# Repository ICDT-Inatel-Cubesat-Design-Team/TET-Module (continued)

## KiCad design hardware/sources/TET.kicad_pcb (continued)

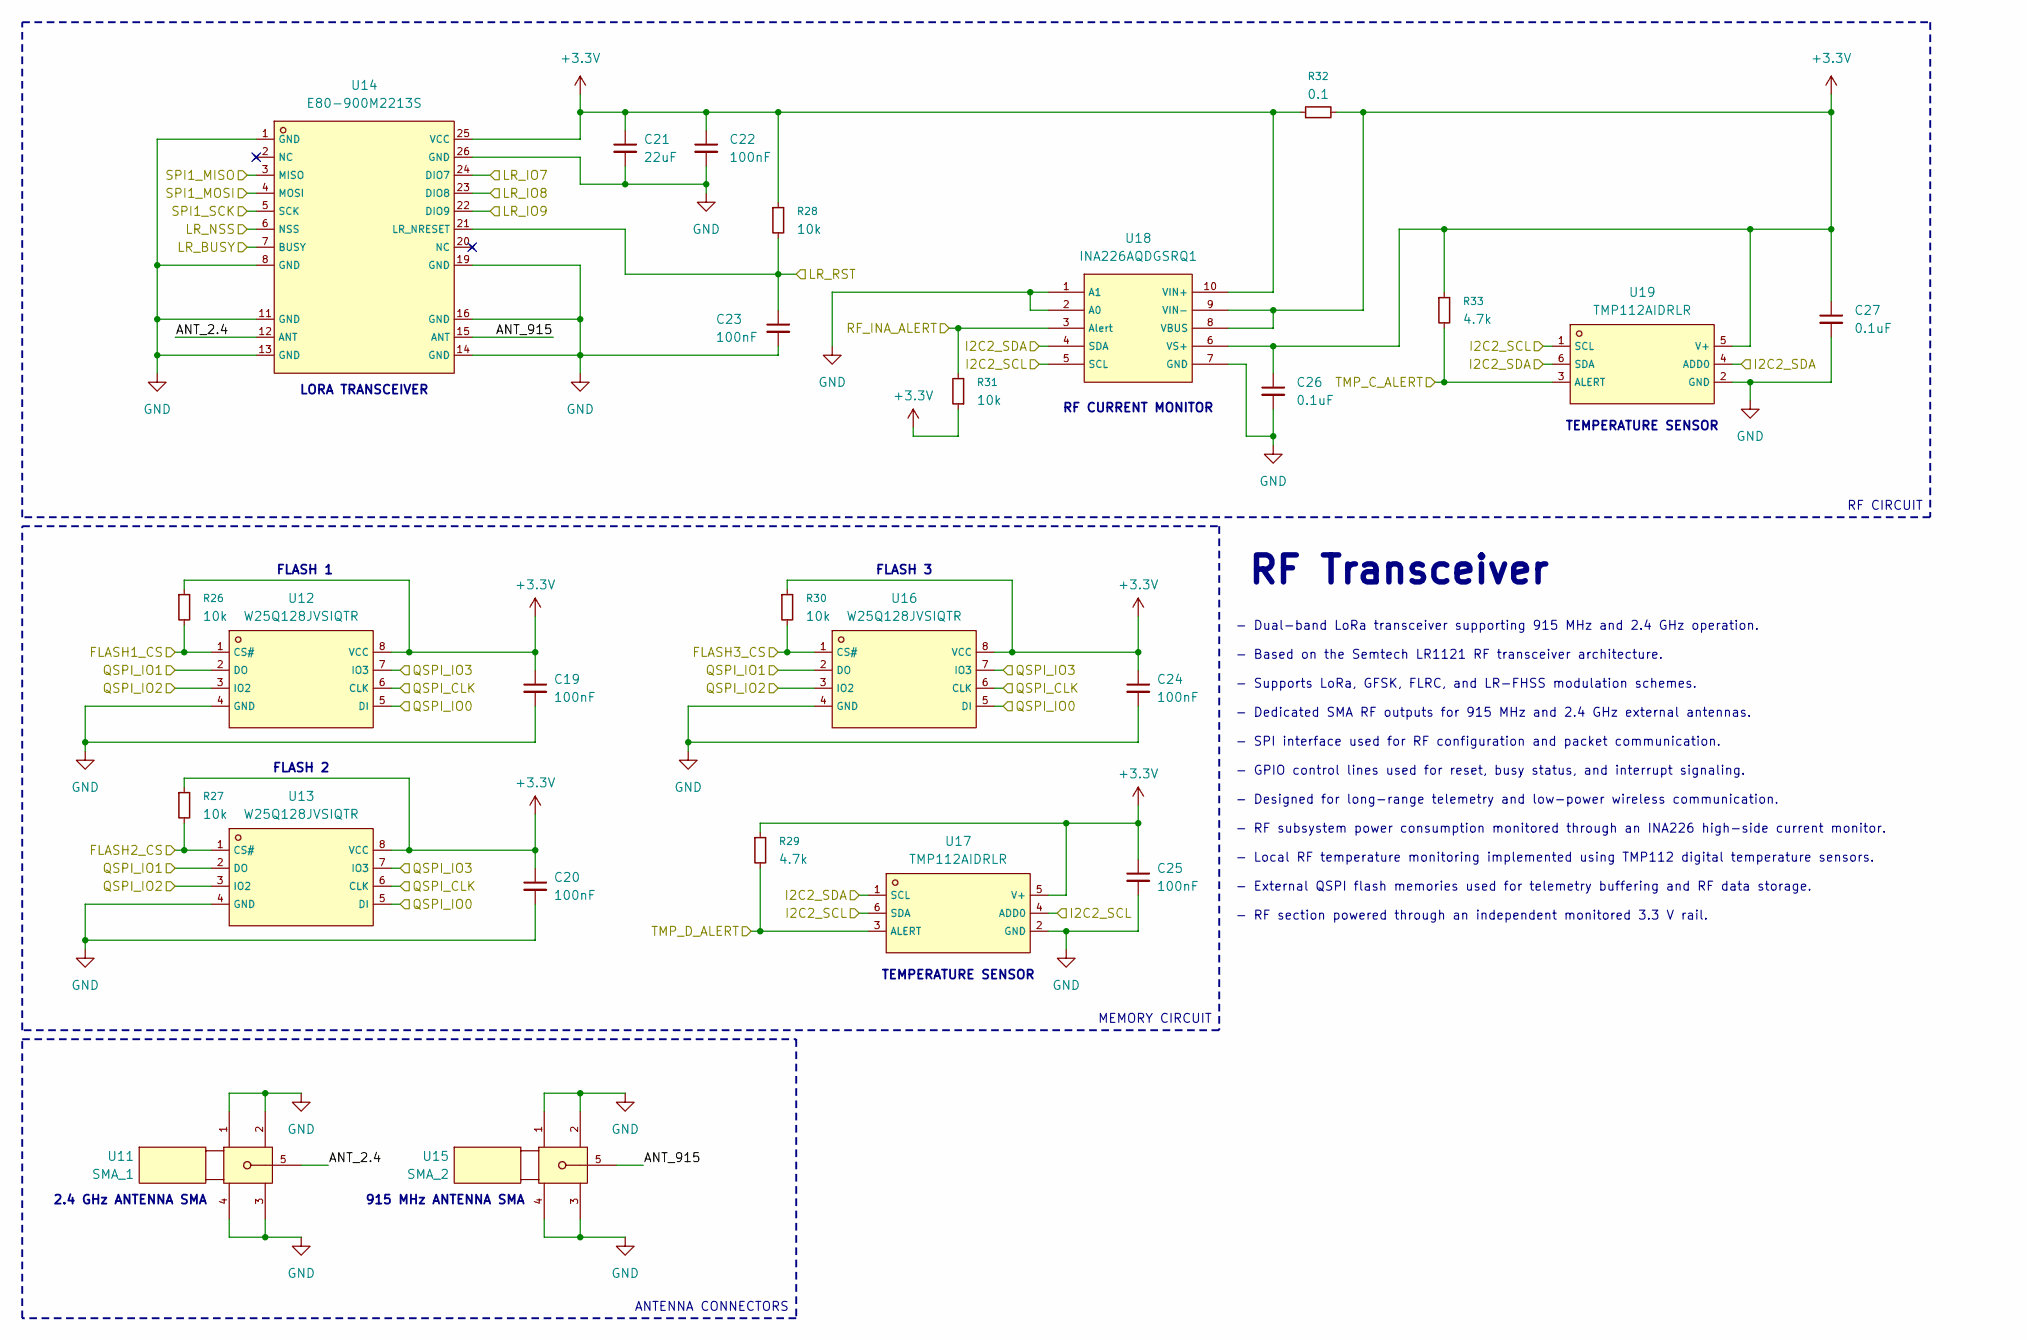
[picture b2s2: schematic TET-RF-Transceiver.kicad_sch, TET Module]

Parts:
C19, C20, C22, C23, C24, C25: 100nF; C_0603_1608Metric
C21: 22uF; C_0603_1608Metric
C26, C27: 0.1uF; C_0603_1608Metric
R26, R27, R28, R30, R31: 10k; R_0603_1608Metric
R29, R33: 4.7k; R_0603_1608Metric
R32: 0.1; R_1206_3216Metric
U11: SMA_1; SMA-TH_SMA-KWE_C7498154; LCSC C7498154
U12, U13, U16: W25Q128JVSIQTR; SOIC-8_L5.3-W5.3-P1.27-LS8.0-BL; LCSC C97521
U14: E80-900M2213S; WIFIM-SMD_22P-L26.0-W16.0-P1.27-TL; LCSC C42464134
U15: SMA_2; SMA-TH_SMA-KWE_C7498154; LCSC C7498154
U17, U19: TMP112AIDRLR; SOT-563_L1.6-W1.2-P0.50-LS1.6-BR; LCSC C28927
U18: INA226AQDGSRQ1; VSSOP-10_L3.0-W3.0-P0.50-LS4.9-BL; LCSC C2653835

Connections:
+3.3V: C19.1, C20.1, C21.1, C22.1, C24.1, C25.1, C26.1, C27.1, R26.1, R27.1, R28.1, R29.1, R30.1, R31.1, R32.1, R32.2, R33.1, U12.8 (VCC), U13.8 (VCC), U14.25 (VCC), U16.8 (VCC), U17.5 (V+), U18.6 (VS+), U18.8 (VBUS), U18.9 (VIN-), U18.10 (VIN+), U19.5 (V+); also elsewhere on the board
/FLASH1_CS: R26.2, U12.1 (CS#); also elsewhere on the board
/FLASH2_CS: R27.2, U13.1 (CS#); also elsewhere on the board
/FLASH3_CS: R30.2, U16.1 (CS#); also elsewhere on the board
/I2C2_SCL: U17.4 (ADD0), U17.6 (SDA), U18.5 (SCL), U19.1 (SCL); also elsewhere on the board
/I2C2_SDA: U17.1 (SCL), U18.4 (SDA), U19.4 (ADD0), U19.6 (SDA); also elsewhere on the board
/LR_BUSY: U14.7 (BUSY); also elsewhere on the board
/LR_IO7: U14.24 (DIO7); also elsewhere on the board
/LR_IO8: U14.23 (DIO8); also elsewhere on the board
/LR_IO9: U14.22 (DIO9); also elsewhere on the board
/LR_NSS: U14.6 (NSS); also elsewhere on the board
/LR_RST: C23.1, R28.2, U14.21 (LR_NRESET); also elsewhere on the board
/QSPI_CLK: U12.6 (CLK), U13.6 (CLK), U16.6 (CLK); also elsewhere on the board
/QSPI_IO0: U12.5 (DI), U13.5 (DI), U16.5 (DI); also elsewhere on the board
/QSPI_IO1: U12.2 (DO), U13.2 (DO), U16.2 (DO); also elsewhere on the board
/QSPI_IO2: U12.3 (IO2), U13.3 (IO2), U16.3 (IO2); also elsewhere on the board
/QSPI_IO3: U12.7 (IO3), U13.7 (IO3), U16.7 (IO3); also elsewhere on the board
/RF_INA_ALERT: R31.2, U18.3 (Alert); also elsewhere on the board
/RF_Transceiver/ANT_2.4: U11.5, U14.12 (ANT)
/RF_Transceiver/ANT_915: U14.15 (ANT), U15.5
/SPI1_MISO: U14.3 (MISO); also elsewhere on the board
/SPI1_MOSI: U14.4 (MOSI); also elsewhere on the board
/SPI1_SCK: U14.5 (SCK); also elsewhere on the board
/TMP_C_ALERT: R33.2, U19.3 (ALERT); also elsewhere on the board
/TMP_D_ALERT: R29.2, U17.3 (ALERT); also elsewhere on the board
GND: C19.2, C20.2, C21.2, C22.2, C23.2, C24.2, C25.2, C26.2, C27.2, U11.1, U11.2, U11.3, U11.4, U12.4 (GND), U13.4 (GND), U14.1 (GND), U14.8 (GND), U14.11 (GND), U14.13 (GND), U14.14 (GND), U14.16 (GND), U14.19 (GND), U14.26 (GND), U15.1, U15.2, U15.3, U15.4, U16.4 (GND), U17.2 (GND), U18.1 (A1), U18.2 (A0), U18.7 (GND), U19.2 (GND); also elsewhere on the board

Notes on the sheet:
TEMPERATURE SENSOR
FLASH 2
915 MHz ANTENNA SMA
2.4 GHz ANTENNA SMA
FLASH 1
LORA TRANSCEIVER
RF CURRENT MONITOR
FLASH 3
RF Transceiver
MEMORY CIRCUIT
- Dual-band LoRa transceiver supporting 915 MHz and 2.4 GHz operation. - Based on the Semtech LR1121 RF transceiver architecture. - Supports LoRa, GFSK, FLRC, and LR-FHSS modulation schemes. - Dedicated SMA RF outputs for 915 MHz and 2.4 GHz external antennas. - SPI interface used for RF configurat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
ANTENNA CONNECTORS
RF CIRCUIT

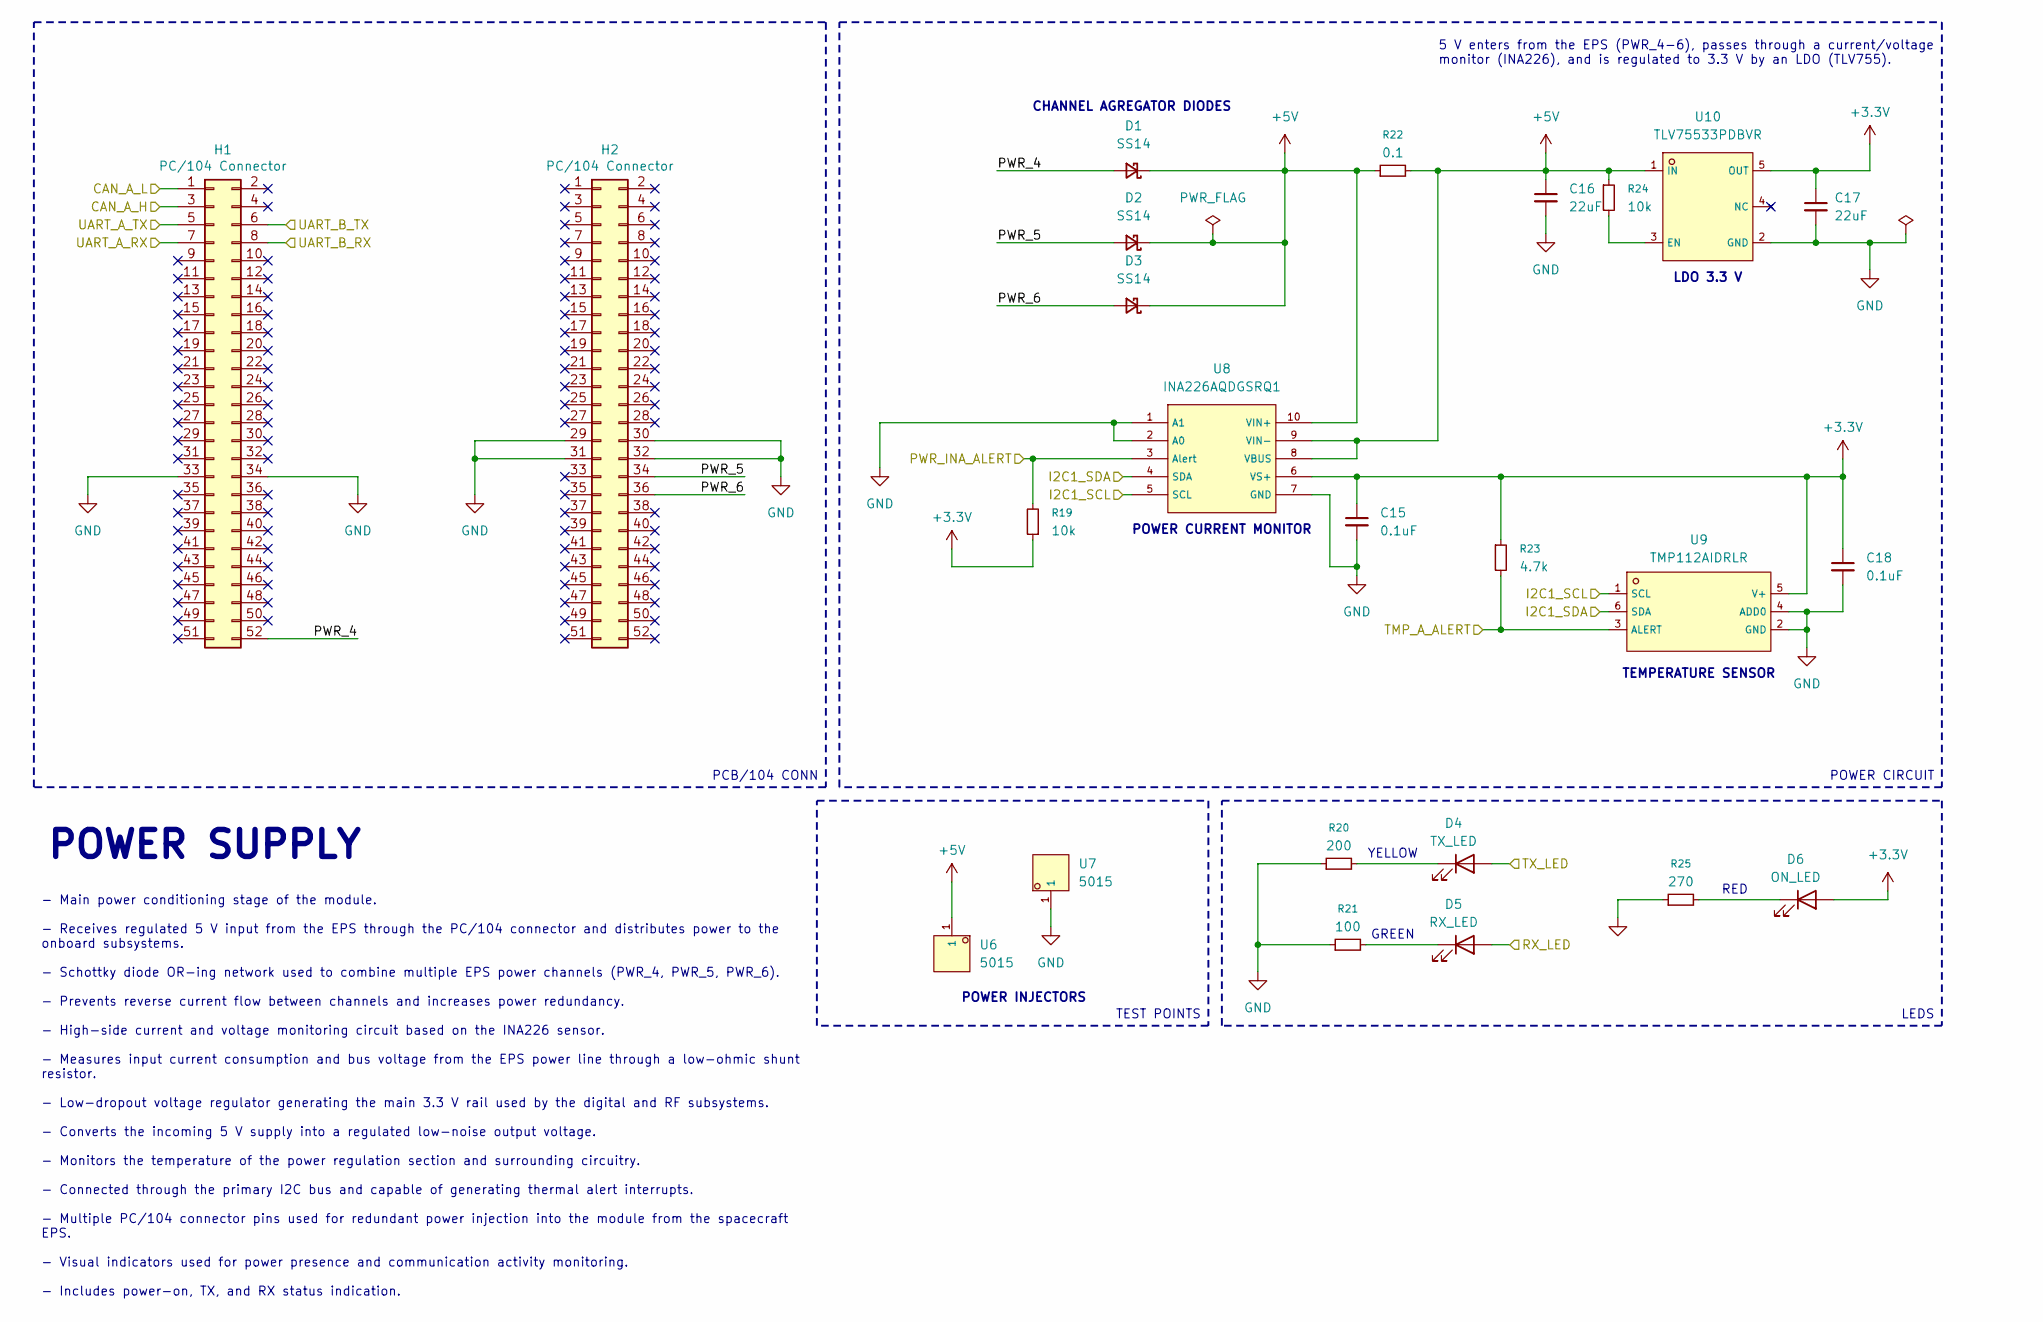
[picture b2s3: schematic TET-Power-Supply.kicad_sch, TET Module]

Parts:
C15, C18: 0.1uF; C_0603_1608Metric
C16, C17: 22uF; C_0603_1608Metric
D1, D2, D3: SS14; D_SMA; LCSC C2480
D4: TX_LED; LED_0805_2012Metric; LCSC C2296
D5: RX_LED; LED_0805_2012Metric; LCSC C2297
D6: ON_LED; LED_0805_2012Metric; LCSC C84256
H1, H2: PC/104 Connector; PinHeader_2x26_P2.54mm_Vertical
R19, R24: 10k; R_0603_1608Metric
R20: 200; R_0603_1608Metric
R21: 100; R_0603_1608Metric
R22: 0.1; R_1206_3216Metric
R23: 4.7k; R_0603_1608Metric
R25: 270; R_0603_1608Metric
U6, U7: 5015; TEST-SMD_L2.7-W1.0; LCSC C2906768
U8: INA226AQDGSRQ1; VSSOP-10_L3.0-W3.0-P0.50-LS4.9-BL; LCSC C2653835
U9: TMP112AIDRLR; SOT-563_L1.6-W1.2-P0.50-LS1.6-BR; LCSC C28927
U10: TLV75533PDBVR; SOT-23-5_L3.0-W1.7-P0.95-LS2.8-BR; LCSC C404027

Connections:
+3.3V: C15.1, C17.1, C18.1, D6.2 (A), R19.1, R23.1, U8.6 (VS+), U9.5 (V+), U10.5 (OUT); also elsewhere on the board
+5V: C16.1, D1.1 (K), D2.1 (K), D3.1 (K), R22.1, R22.2, R24.1, U6.1 (1_1), U8.8 (VBUS), U8.9 (VIN-), U8.10 (VIN+), U10.1 (IN)
/CAN_A_H: H1.3; also elsewhere on the board
/CAN_A_L: H1.1; also elsewhere on the board
/I2C1_SCL: U8.5 (SCL), U9.1 (SCL); also elsewhere on the board
/I2C1_SDA: U8.4 (SDA), U9.6 (SDA); also elsewhere on the board
/PWR_INA_ALERT: R19.2, U8.3 (Alert); also elsewhere on the board
/Power_Supply/PWR_4: D1.2 (A), H1.52
/Power_Supply/PWR_5: D2.2 (A), H2.34
/Power_Supply/PWR_6: D3.2 (A), H2.36
/RX_LED: D5.2 (A); also elsewhere on the board
/TMP_A_ALERT: R23.2, U9.3 (ALERT); also elsewhere on the board
/TX_LED: D4.2 (A); also elsewhere on the board
/UART_A_RX: H1.7; also elsewhere on the board
/UART_A_TX: H1.5; also elsewhere on the board
/UART_B_RX: H1.8; also elsewhere on the board
/UART_B_TX: H1.6; also elsewhere on the board
GND: C15.2, C16.2, C17.2, C18.2, H1.33, H1.34, H2.29, H2.30, H2.31, H2.32, R20.1, R21.1, R25.1, U7.1 (1_1), U8.1 (A1), U8.2 (A0), U8.7 (GND), U9.2 (GND), U9.4 (ADD0), U10.2 (GND); also elsewhere on the board
unnamed: D4.1 (K), R20.2
unnamed: D5.1 (K), R21.2
unnamed: D6.1 (K), R25.2
unnamed: R24.2, U10.3 (EN)

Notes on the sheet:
POWER INJECTORS
POWER SUPPLY
TEMPERATURE SENSOR
5 V enters from the EPS (PWR_4-6), passes through a current/voltage monitor (INA226), and is regulated to 3.3 V by an LDO (TLV755).
POWER CURRENT MONITOR
RED
LDO 3.3 V
YELLOW
CHANNEL AGREGATOR DIODES
GREEN
TEST POINTS
PCB/104 CONN
- Main power conditioning stage of the module. - Receives regulated 5 V input from the EPS through the PC/104 connector and distributes power to the onboard subsystems. - Schottky diode OR-ing network used to combine multiple EPS power channels (PWR_4, PWR_5, PWR_6). - Prevents reverse current flow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
POWER CIRCUIT
LEDS

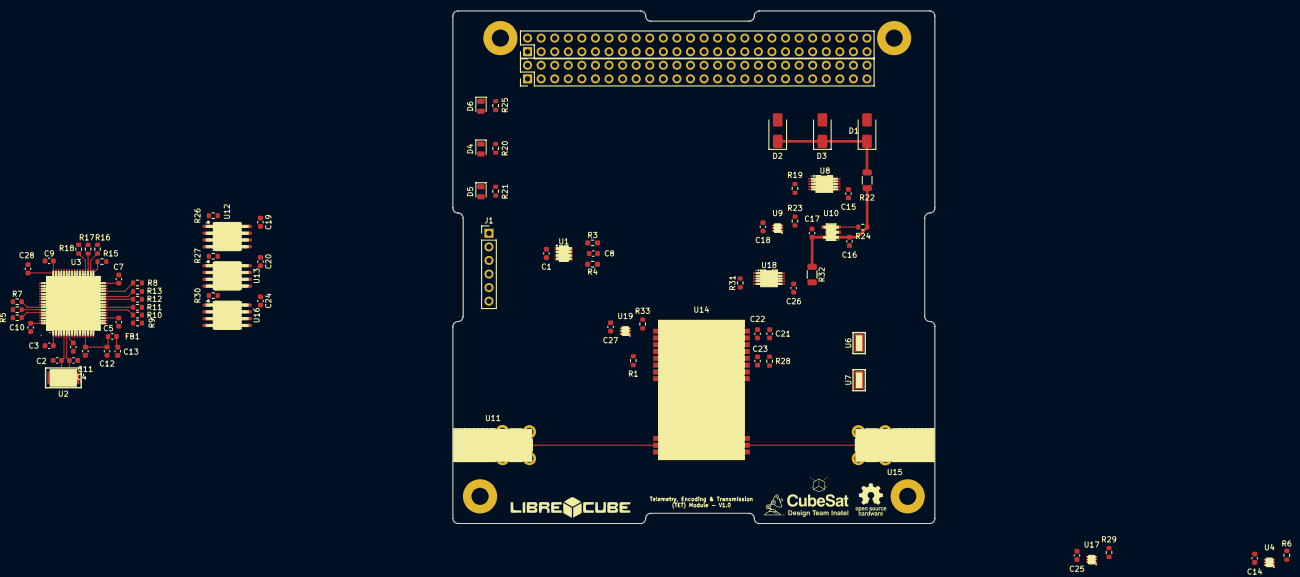
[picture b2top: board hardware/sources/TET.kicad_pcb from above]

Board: 4 copper layers, 90.2 x 95.9 mm, 93 parts (0 on the bottom side), 64 nets.

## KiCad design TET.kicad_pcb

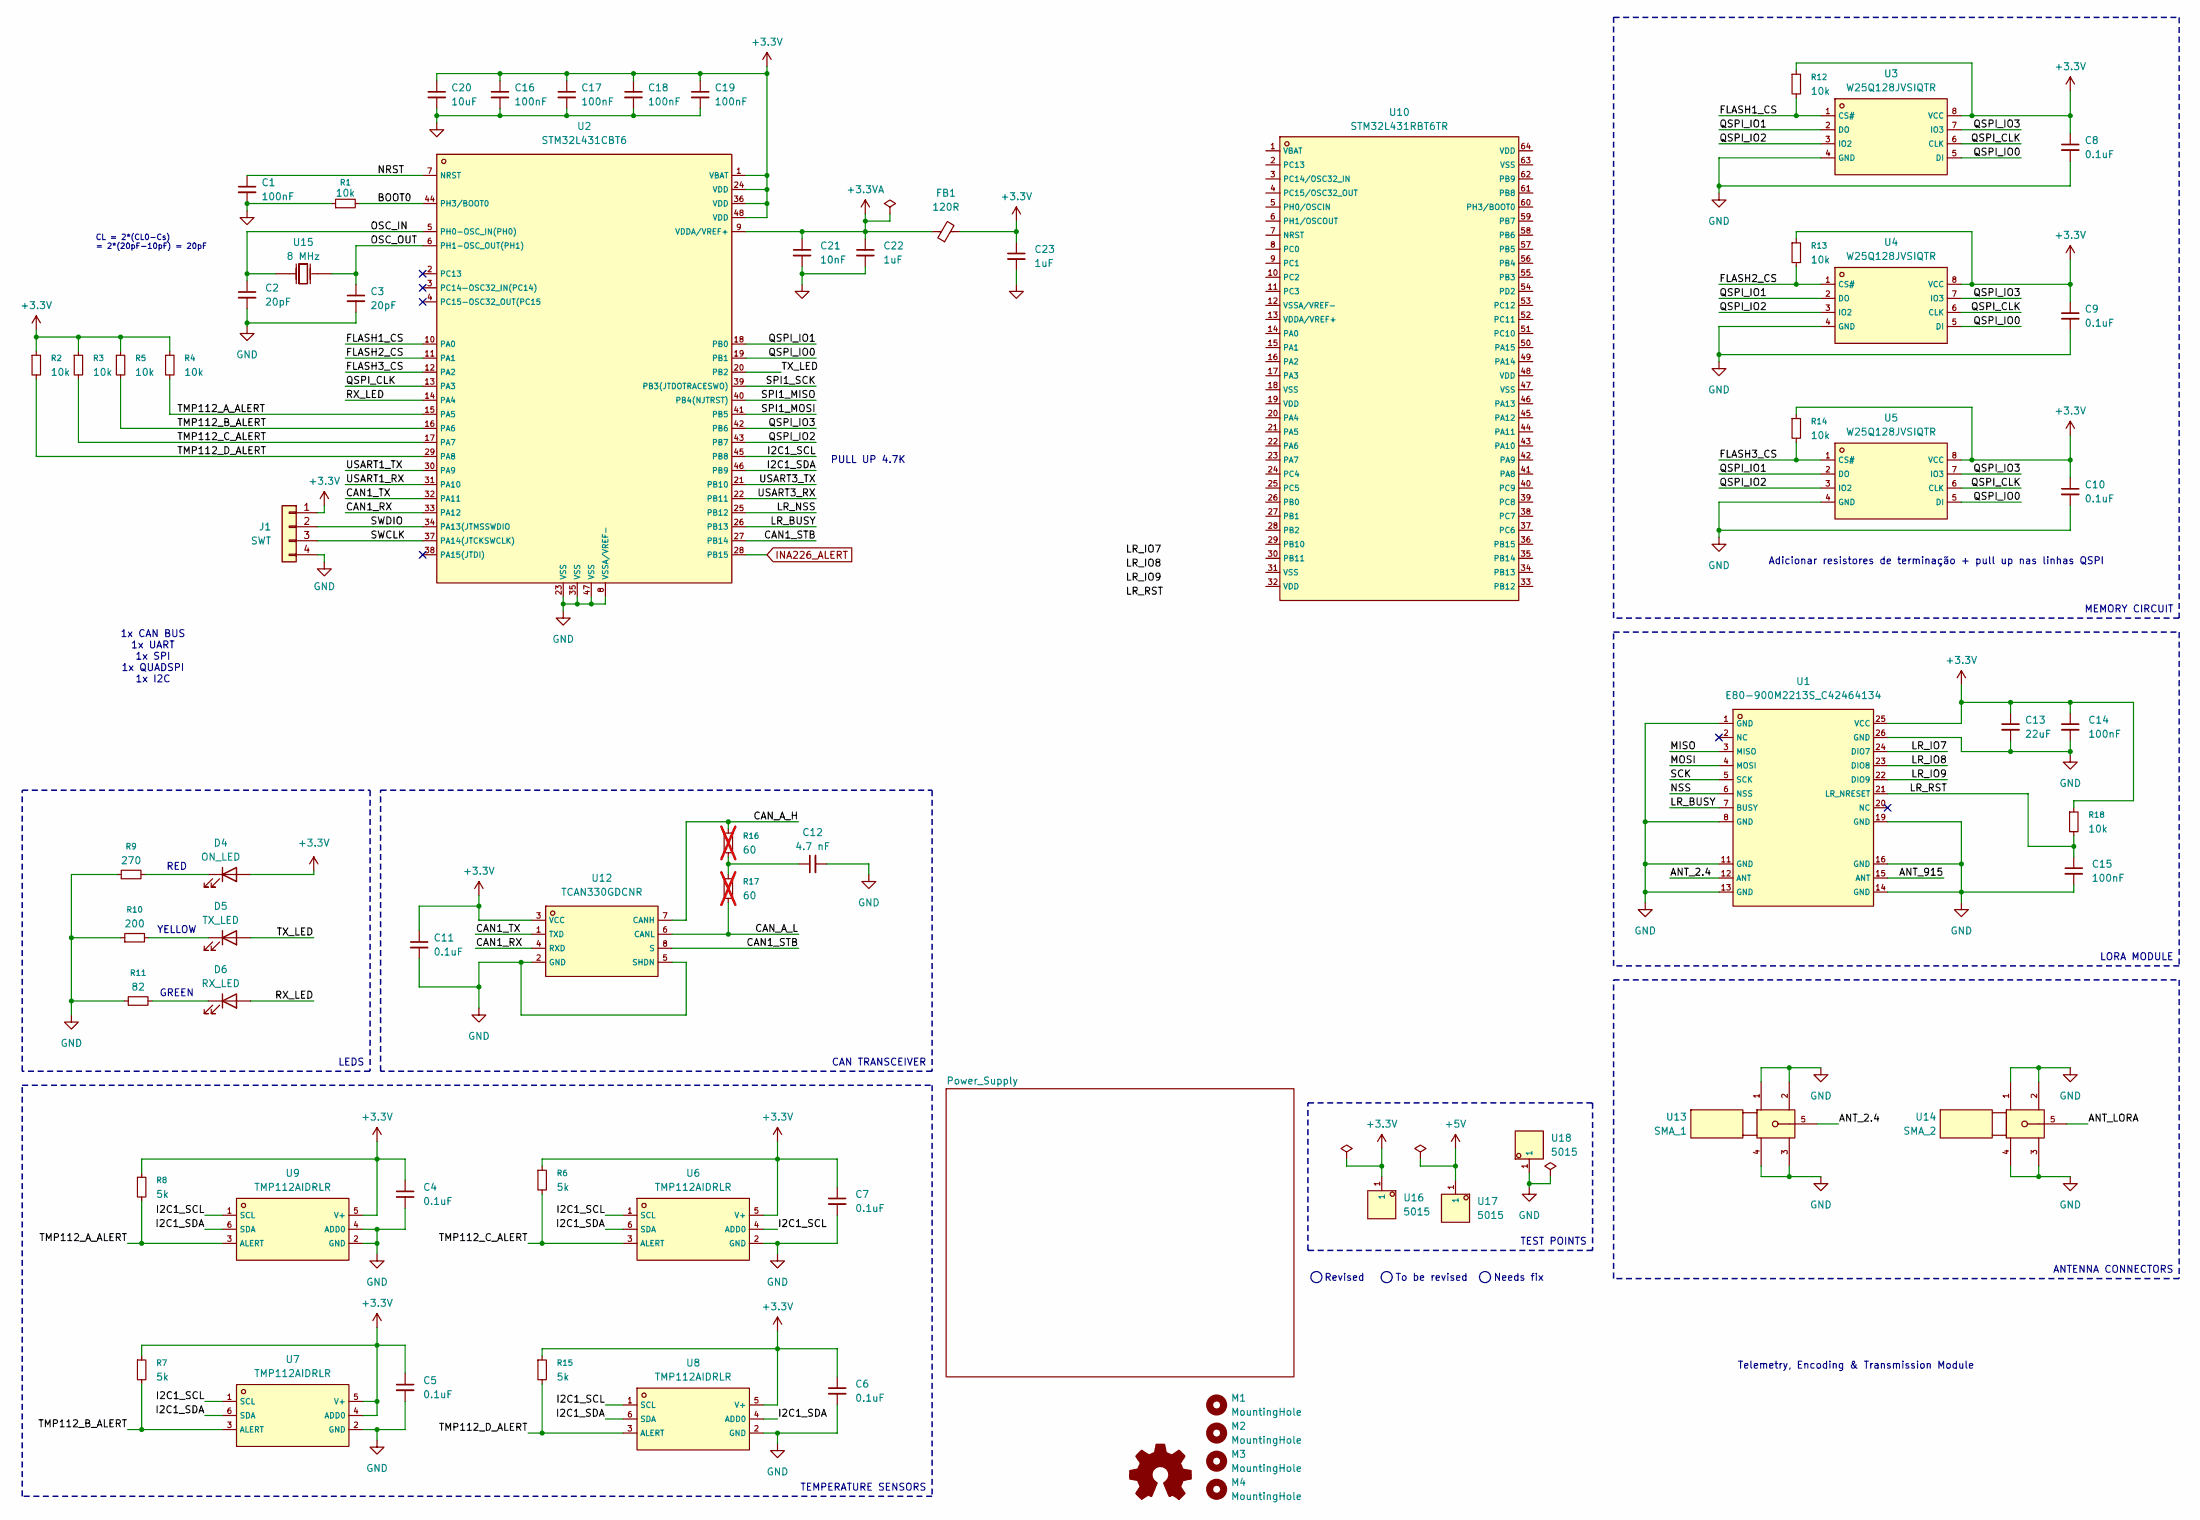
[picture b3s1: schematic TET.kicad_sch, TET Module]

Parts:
C1, C14, C15, C16, C17, C18, C19: 100nF; C_0603_1608Metric
C2, C3: 20pF; C_0603_1608Metric
C4, C5, C6, C7, C8, C9, C10, C11: 0.1uF; C_0603_1608Metric
C12: 4.7 nF; C_0603_1608Metric
C13: 22uF; C_0603_1608Metric
C20: 10uF; C_0603_1608Metric
C21: 10nF; C_0603_1608Metric
C22, C23: 1uF; C_0603_1608Metric
D4: ON_LED; LED_0805_2012Metric; LCSC C84256
D5: TX_LED; LED_0805_2012Metric; LCSC C2296
D6: RX_LED; LED_0805_2012Metric; LCSC C2297
FB1: 120R; L_0603_1608Metric; LCSC C14709
J1: SWT; PinHeader_1x04_P2.54mm_Vertical
M1, M2, M3, M4: MountingHole; MountingHole_3.2mm_M3_Pad
R1, R2, R3, R4, R5: 10k
R6, R7, R8, R15: 5k; R_0603_1608Metric
R9: 270; R_0603_1608Metric
R10: 200; R_0603_1608Metric
R11: 82; R_0603_1608Metric
R12, R13, R14, R18: 10k; R_0603_1608Metric
R16, R17: 60; R_0805_2012Metric_Pad1.20x1.40mm_HandSolder; not fitted
REF1: Logo_Open_Hardware_Small; OSHW-Logo_5.7x6mm_SilkScreen
U1: E80-900M2213S_C42464134; WIFIM-SMD_22P-L26.0-W16.0-P1.27-TL; LCSC C42464134
U2: STM32L431CBT6; LQFP-48_L7.0-W7.0-P0.50-LS9.0-BL; LCSC C277951
U3, U4, U5: W25Q128JVSIQTR; SOIC-8_L5.3-W5.3-P1.27-LS8.0-BL; LCSC C97521
U6, U7, U8, U9: TMP112AIDRLR; SOT-563_L1.6-W1.2-P0.50-LS1.6-BR; LCSC C28927
U10: STM32L431RBT6TR; LQFP-64_L10.0-W10.0-P0.50-LS12.0-BL; LCSC C2053549
U12: TCAN330GDCNR; SOT-23-8_L2.9-W1.6-P0.65-LS2.8-BL; LCSC C191006
U13: SMA_1; SMA-TH_SMA-KWE_C7498154; LCSC C7498154
U14: SMA_2; SMA-TH_SMA-KWE_C7498154; LCSC C7498154
U15: 8 MHz; CRYSTAL-SMD_L5.0-W3.2; LCSC C115962
U16, U17, U18: 5015; TEST-SMD_L2.7-W1.0; LCSC C2906768

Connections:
+3.3V: C4.1, C5.1, C6.1, C7.1, C8.1, C9.1, C10.1, C11.1, C13.1, C14.1, C16.1, C17.1, C18.1, C19.1, C20.1, C23.1, D4.2 (A), FB1.2, J1.1, R2.1, R3.1, R4.1, R5.1, R6.1, R7.1, R8.1, R12.1, R13.1, R14.1, R15.1, R18.1, U1.25 (VCC), U2.1 (VBAT), U2.24 (VDD), U2.36 (VDD), U2.48 (VDD), U3.8 (VCC), U4.8 (VCC), U5.8 (VCC), U6.5 (V+), U7.4 (ADD0), U7.5 (V+), U8.5 (V+), U9.5 (V+), U12.3 (VCC), U16.1; also elsewhere on the board
+3.3VA: C21.1, C22.1, FB1.1, U2.9 (VDDA/VREF+)
+5V: U17.1; also elsewhere on the board
/ANT_2.4: U1.12 (ANT), U13.5
/ANT_915: U1.15 (ANT)
/ANT_LORA: U14.5
/BOOT0: R1.2, U2.44 (PH3/BOOT0)
/CAN1_RX: U2.33 (PA12), U12.4 (RXD)
/CAN1_STB: U2.27 (PB14), U12.8 (S)
/CAN1_TX: U2.32 (PA11), U12.1 (TXD)
/CAN_A_H: R16.1, U12.7 (CANH); also elsewhere on the board
/CAN_A_L: R17.2, U12.6 (CANL); also elsewhere on the board
/FLASH1_CS: R12.2, U2.10 (PA0), U3.1 (CS#)
/FLASH2_CS: R13.2, U2.11 (PA1), U4.1 (CS#)
/FLASH3_CS: R14.2, U2.12 (PA2), U5.1 (CS#)
/I2C1_SCL: U2.45 (PB8), U6.1 (SCL), U6.4 (ADD0), U7.1 (SCL), U8.1 (SCL), U9.1 (SCL)
/I2C1_SDA: U2.46 (PB9), U6.6 (SDA), U7.6 (SDA), U8.4 (ADD0), U8.6 (SDA), U9.6 (SDA)
/LR_BUSY: U1.7 (BUSY), U2.26 (PB13)
/LR_IO7: U1.24 (DIO7)
/LR_IO8: U1.23 (DIO8)
/LR_IO9: U1.22 (DIO9)
/LR_NSS: U2.25 (PB12)
/LR_RST: C15.1, R18.2, U1.21 (LR_NRESET)
/MISO: U1.3 (MISO)
/MOSI: U1.4 (MOSI)
/NRST: C1.1, U2.7 (NRST)
/NSS: U1.6 (NSS)
/OSC_IN: C2.1, U2.5 (PH0-OSC_IN(PH0)), U15.2 (OSC2)
/OSC_OUT: C3.1, U2.6 (PH1-OSC_OUT(PH1)), U15.1 (OSC1)
/QSPI_CLK: U2.13 (PA3), U3.6 (CLK), U4.6 (CLK), U5.6 (CLK)
/QSPI_IO0: U2.19 (PB1), U3.5 (DI), U4.5 (DI), U5.5 (DI)
/QSPI_IO1: U2.18 (PB0), U3.2 (DO), U4.2 (DO), U5.2 (DO)
/QSPI_IO2: U2.43 (PB7), U3.3 (IO2), U4.3 (IO2), U5.3 (IO2)
/QSPI_IO3: U2.42 (PB6), U3.7 (IO3), U4.7 (IO3), U5.7 (IO3)
/RX_LED: D6.2 (A), U2.14 (PA4)
/SCK: U1.5 (SCK)
/SPI1_MISO: U2.40 (PB4(NJTRST))
/SPI1_MOSI: U2.41 (PB5)
/SPI1_SCK: U2.39 (PB3(JTDOTRACESWO))
/SWCLK: J1.3, U2.37 (PA14(JTCKSWCLK))
/SWDIO: J1.2, U2.34 (PA13(JTMSSWDIO)
/TMP112_C_ALERT: R3.2, R6.2, U2.17 (PA7), U6.3 (ALERT)
/TMP112_D_ALERT: R2.2, R15.2, U2.29 (PA8), U8.3 (ALERT)
/TX_LED: D5.2 (A), U2.20 (PB2)
/USART1_RX: U2.31 (PA10)
/USART1_TX: U2.30 (PA9)
/USART3_RX: U2.22 (PB11)
/USART3_TX: U2.21 (PB10)
GND: C1.2, C2.2, C3.2, C4.2, C5.2, C6.2, C7.2, C8.2, C9.2, C10.2, C11.2, C12.2, C13.2, C14.2, C15.2, C16.2, C17.2, C18.2, C19.2, C20.2, C21.2, C22.2, C23.2, J1.4, R1.1, R9.1, R10.1, R11.1, U1.1 (GND), U1.8 (GND), U1.11 (GND), U1.13 (GND), U1.14 (GND), U1.16 (GND), U1.19 (GND), U1.26 (GND), U2.8 (VSSA/VREF-), U2.23 (VSS), U2.35 (VSS), U2.47 (VSS), U3.4 (GND), U4.4 (GND), U5.4 (GND), U6.2 (GND), U7.2 (GND), U8.2 (GND), U9.2 (GND), U9.4 (ADD0), U12.2 (GND), U12.5 (SHDN), U13.1, U13.2, U13.3, U13.4, U14.1, U14.2, U14.3, U14.4, U18.1; also elsewhere on the board
INA226_ALERT: U2.28 (PB15)
unnamed: C12.1, R16.2, R17.1
unnamed: D4.1 (K), R9.2
unnamed: D5.1 (K), R10.2
unnamed: D6.1 (K), R11.2

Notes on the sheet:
1x CAN BUS 1x UART 1x SPI 1x QUADSPI 1x I2C
Revised
CL = 2*(CL0-Cs) = 2*(20pF-10pF) = 20pF
Needs fix
Adicionar resistores de terminação + pull up nas linhas QSPI
GREEN
YELLOW
RED
PULL UP 4.7K
To be revised
Telemetry, Encoding & Transmission Module
TEMPERATURE SENSORS
LORA MODULE
TEST POINTS
CAN TRANSCEIVER
LEDS
ANTENNA CONNECTORS
MEMORY CIRCUIT

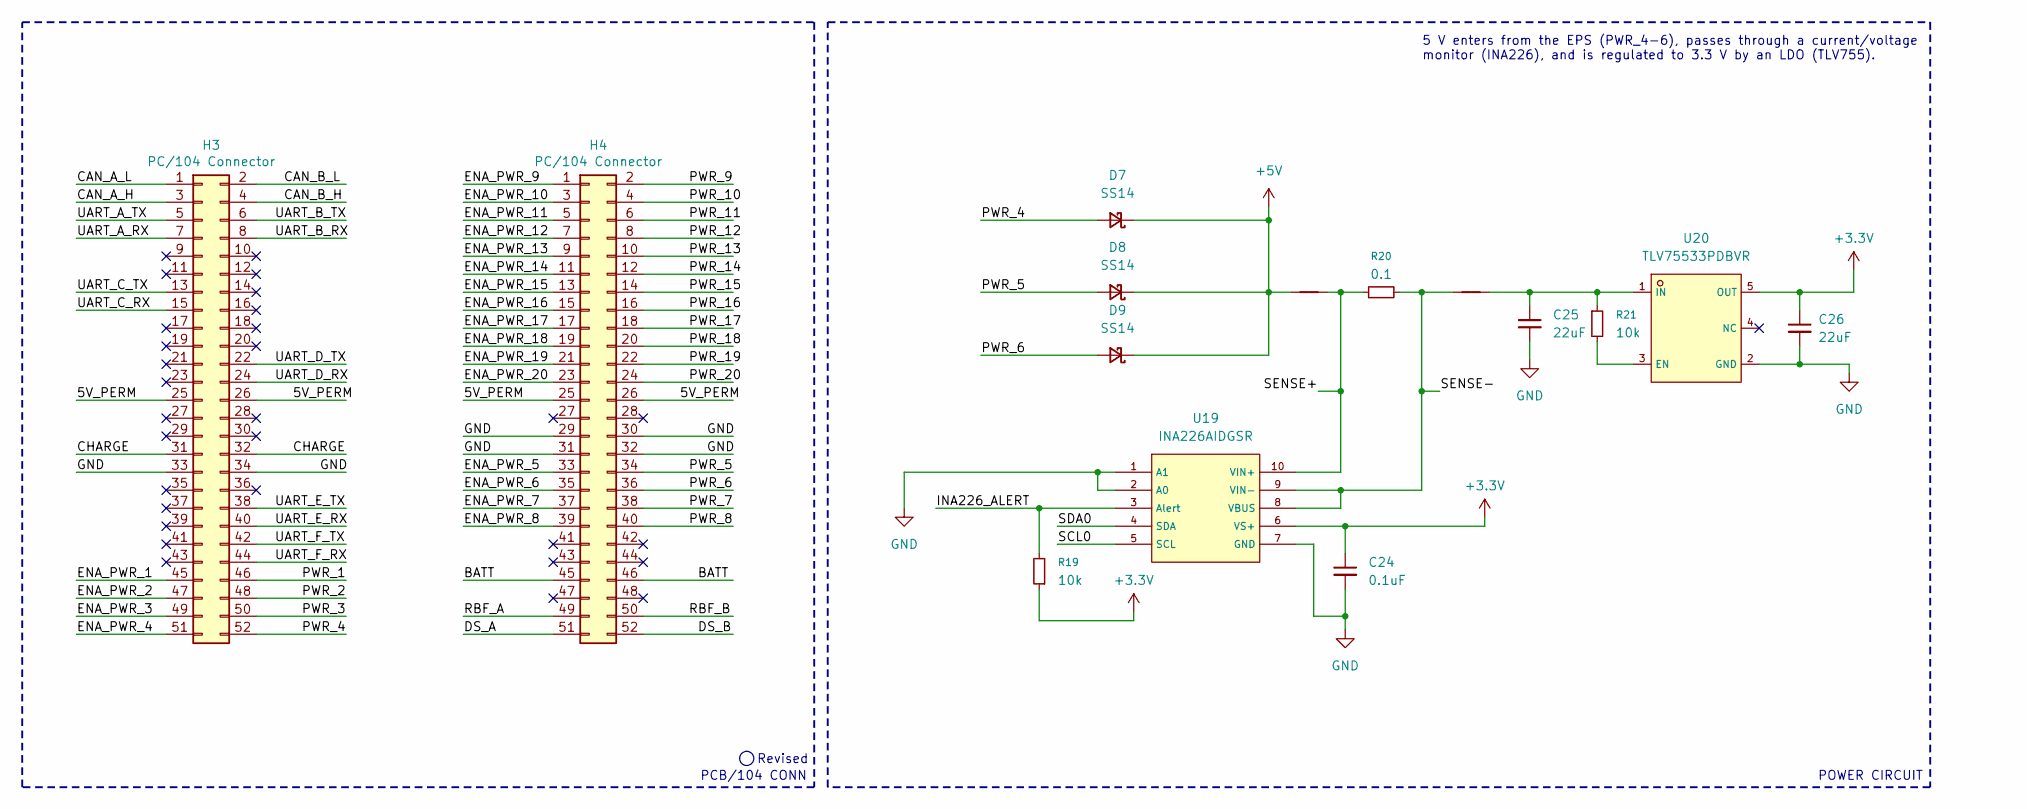
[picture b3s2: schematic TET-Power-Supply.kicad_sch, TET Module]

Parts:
C24: 0.1uF; C_0603_1608Metric
C25, C26: 22uF; C_0603_1608Metric
D7, D8, D9: SS14; D_SMA; LCSC C2480
H3, H4: PC/104 Connector; PinSocket_2x26_P2.54mm_Vertical
NT3, NT4: NetTie_2
R19, R21: 10k; R_0603_1608Metric
R20: 0.1; R_0603_1608Metric
U19: INA226AIDGSR; MSOP-10_L3.0-W3.0-P0.50-LS5.0-BL; LCSC C49851
U20: TLV75533PDBVR; SOT-23-5_L3.0-W1.7-P0.95-LS2.8-BR; LCSC C404027

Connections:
+3.3V: C24.1, C26.1, R19.1, U19.6 (VS+), U20.5 (OUT); also elsewhere on the board
+5V: D7.1 (K), D8.1 (K), D9.1 (K), NT3.1; also elsewhere on the board
/Power_Supply/INA226_ALERT: R19.2, U19.3 (Alert)
/Power_Supply/PWR_4: D7.2 (A), H3.52
/Power_Supply/PWR_5: D8.2 (A), H4.34
/Power_Supply/PWR_6: D9.2 (A), H4.36
/Power_Supply/SCL0: U19.5 (SCL)
/Power_Supply/SDA0: U19.4 (SDA)
/Power_Supply/SENSE+: NT3.2, R20.1, U19.10 (VIN+)
/Power_Supply/SENSE-: NT4.1, R20.2, U19.8 (VBUS), U19.9 (VIN-)
GND: C24.2, C25.2, C26.2, U19.1 (A1), U19.2 (A0), U19.7 (GND), U20.2 (GND); also elsewhere on the board
unnamed: H3.25, H3.26, H4.25, H4.26
unnamed: H3.31, H3.32
unnamed: H3.33, H3.34, H4.29, H4.30, H4.31, H4.32
unnamed: H4.45, H4.46
unnamed: R21.2, U20.3 (EN)
unnamed: C25.1, NT4.2, R21.1, U20.1 (IN)

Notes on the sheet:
5 V enters from the EPS (PWR_4-6), passes through a current/voltage monitor (INA226), and is regulated to 3.3 V by an LDO (TLV755).
Revised
PCB/104 CONN
POWER CIRCUIT

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
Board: 4 copper layers, 78 parts (0 on the bottom side), 45 nets, no tracks yet.

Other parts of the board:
H1, H2: PC/104 Connector; PinHeader_2x26_P2.54mm_Vertical

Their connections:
/5V_PERM: H1.25, H1.26, H2.25, H2.26
/BATT: H2.45, H2.46
/CAN_A_H: H1.3; also elsewhere on the board
/CAN_A_L: H1.1; also elsewhere on the board
/CHARGE: H1.31, H1.32
GND: H1.33, H1.34, H2.29, H2.30, H2.31, H2.32; also elsewhere on the board

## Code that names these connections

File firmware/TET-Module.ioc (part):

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Mcu.Name=STM32L431C(B-C)Tx
Mcu.Package=LQFP48
Mcu.UserName=STM32L431CCTx
PA0.GPIOParameters=GPIO_Label
PA0.GPIO_Label=TX_LED
PA0.Signal=GPIO_Output
PA1.Mode=Full_Duplex_Master
PA1.Signal=SPI1_SCK
PA10.Mode=I2C
PA10.Signal=I2C1_SDA
PA11.Mode=CAN_Activate
PA11.Signal=CAN1_RX
PA12.Mode=CAN_Activate
PA12.Signal=CAN1_TX
PA13\ (JTMS-SWDIO).Mode=Trace_Asynchronous_SW
PA13\ (JTMS-SWDIO).Signal=SYS_JTMS-SWDIO
PA14\ (JTCK-SWCLK).Mode=Trace_Asynchronous_SW
PA14\ (JTCK-SWCLK).Signal=SYS_JTCK-SWCLK
PA2.GPIOParameters=GPIO_Label
PA2.GPIO_Label=RX_LED
PA2.Signal=GPIO_Output
PA3.GPIOParameters=GPIO_Label
PA3.GPIO_Label=FLASH1_CS
PA3.Signal=GPIO_Output
PA4.GPIOParameters=GPIO_Label
PA4.GPIO_Label=FLASH2_CS
PA4.Signal=GPIO_Output
PA5.GPIOParameters=GPIO_Label
PA5.GPIO_Label=FLASH3_CS
PA5.Signal=GPIO_Output
PA6.Mode=Full_Duplex_Master
PA6.Signal=SPI1_MISO
PA7.Mode=Full_Duplex_Master
PA7.Signal=SPI1_MOSI
PA8.GPIOParameters=GPIO_Label
PA8.GPIO_Label=CAN1_STB
PA8.Signal=GPIO_Output
PA9.Mode=I2C
PA9.Signal=I2C1_SCL
PB0.GPIOParameters=GPIO_Label
PB0.GPIO_Label=TMP_D_ALERT
PB0.Signal=GPXTI0
PB1.GPIOParameters=GPIO_Label
PB1.GPIO_Label=TMP_C_ALERT
PB1.Signal=GPXTI1
PB10.Mode=Full_Duplex_Master
PB10.Signal=SPI2_SCK
PB11.Mode=I2C
PB11.Signal=I2C2_SDA
PB13.Mode=I2C
PB13.Signal=I2C2_SCL
PB14.Mode=Full_Duplex_Master
PB14.Signal=SPI2_MISO
PB15.Mode=Full_Duplex_Master
PB15.Signal=SPI2_MOSI
PB2.GPIOParameters=GPIO_Label
PB2.GPIO_Label=TMP_A_ALERT
PB2.Signal=GPXTI2
PB3\ (JTDO-TRACESWO).Mode=Trace_Asynchronous_SW
PB3\ (JTDO-TRACESWO).Signal=SYS_JTDO-SWO
PB4\ (NJTRST).GPIOParameters=GPIO_Label
PB4\ (NJTRST).GPIO_Label=LR_BUSY
PB4\ (NJTRST).Signal=GPIO_Input
PB5.GPIOParameters=GPIO_Label
PB5.GPIO_Label=LR_NSS
PB5.Signal=GPIO_Output
PB6.GPIOParameters=GPIO_Label
PB6.GPIO_Label=LR_IO7
PB6.Signal=GPXTI6
PB7.GPIOParameters=GPIO_Label
PB7.GPIO_Label=LR_IO8
PB7.Signal=GPXTI7
PB8.GPIOParameters=GPIO_Label
PB8.GPIO_Label=LR_IO9
PB8.Signal=GPXTI8
PB9.GPIOParameters=GPIO_Label
PB9.GPIO_Label=LR_RST
PB9.Signal=GPXTI9
PC13.GPIOParameters=GPIO_Label
PC13.GPIO_Label=RF_INA_ALERT
PC13.Signal=GPXTI13
PC14-OSC32_IN\ (PC14).GPIOParameters=GPIO_Label
PC14-OSC32_IN\ (PC14).GPIO_Label=PWR_INA_ALERT
PC14-OSC32_IN\ (PC14).Signal=GPXTI14
PC15-OSC32_OUT\ (PC15).GPIOParameters=GPIO_Label
PC15-OSC32_OUT\ (PC15).GPIO_Label=TMP_B_ALERT
PC15-OSC32_OUT\ (PC15).Signal=GPXTI15
PH0-OSC_IN\ (PH0).Mode=HSE-External-Oscillator
PH0-OSC_IN\ (PH0).Signal=RCC_OSC_IN
PH1-OSC_OUT\ (PH1).Mode=HSE-External-Oscillator
PH1-OSC_OUT\ (PH1).Signal=RCC_OSC_OUT
RCC.HSE_VALUE=8000000
board=custom

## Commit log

2026-05-03 🎀 Initial commit
2026-05-04 ✨ feat(schematic): start connections for STM32L4
2026-05-04 ✨ feat(schematic): add pinout STM32
2026-05-05 ♻️ ref(schematic): change MCU from 48 pins to 64 pins
2026-05-10 hardware(schematics): upload pre-review schematic
2026-05-11 hardware(schematics): remove 3.3 V power injector #2
2026-05-11 hardware(schematic): link datasheet to all main components #1
2026-05-11 hardware(schematic): fix Electrical Rules Check (ERC)
2026-05-11 hardware(schematic): update documentation for all sheets
2026-05-15 hardware(pcb_design): start PCB design
2026-05-16 hardware(schematic): add bulk capacitor on STM32L4 #5
2026-05-18 feat(schematic): fix double pull-up resistor for LR_BUSY
2026-05-18 hardware(pcb_design): components Micro-Placement
2026-05-30 hardware(pcb_design): MCU components placement
2026-06-09 feat(hardware): implement TET module PCB design and restructure project
2026-06-09 feat(hardware): complete PCB layout and project structure
2026-06-23 feat(hardware): release v1r2
